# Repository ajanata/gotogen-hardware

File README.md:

# Gotogen Hardware

Protogen, the Go way. This repository is the entrypoint for hardware devices.

Highly volatile during active development. For ease of my own development, there are `replace` directives in `go.mod` to use relative paths for the related modules (`go.work` wasn't working for me). I will attempt to keep all the repositories up to date. You will need to either remove the `replace` directives, or have all the repositories checked out next to each other.

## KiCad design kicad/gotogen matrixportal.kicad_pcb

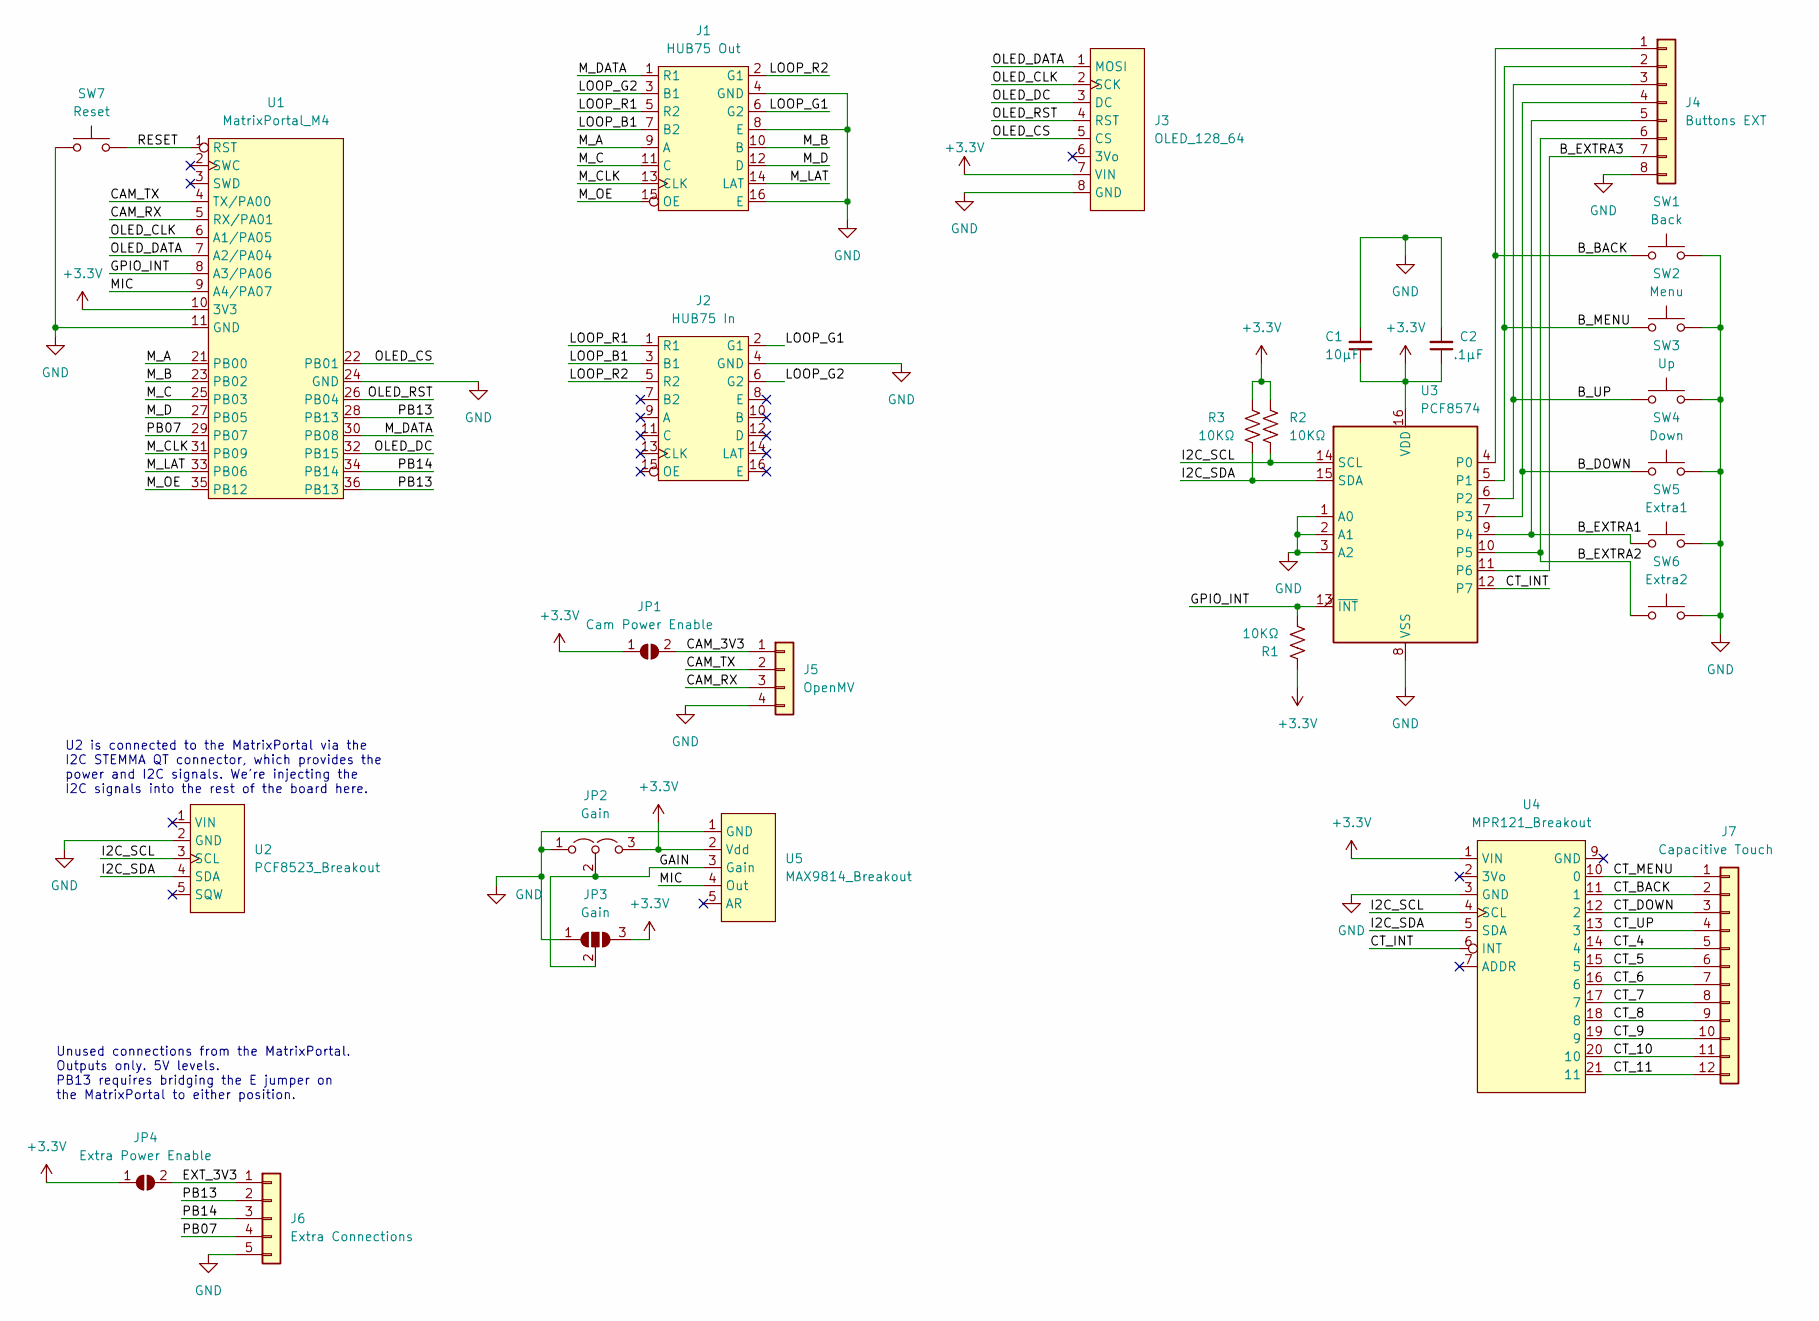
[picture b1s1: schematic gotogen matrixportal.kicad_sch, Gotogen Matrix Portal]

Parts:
C1: 10μF; C_Disc_D5.0mm_W2.5mm_P5.00mm
C2: .1μF; C_Disc_D5.0mm_W2.5mm_P5.00mm
J1: HUB75 Out; PinSocket_2x08_P2.54mm_Vertical
J2: HUB75 In; PinHeader_2x08_P2.54mm_Vertical
J3: OLED_128_64
J4: Buttons EXT; PinHeader_1x08_P2.54mm_Vertical
J5: OpenMV; PinHeader_1x04_P2.54mm_Vertical
J6: Extra Connections; PinHeader_1x05_P2.54mm_Vertical
J7: Capacitive Touch; PinHeader_1x12_P2.54mm_Vertical
JP1: Cam Power Enable; SolderJumper-2_P1.3mm_Open_Pad1.0x1.5mm
JP2: Gain; PinHeader_1x03_P2.54mm_Vertical
JP3: Gain; SolderJumper-3_P1.3mm_Open_Pad1.0x1.5mm_NumberLabels
JP4: Extra Power Enable; SolderJumper-2_P1.3mm_Open_Pad1.0x1.5mm
R1, R2, R3: 10KΩ; R_Axial_DIN0207_L6.3mm_D2.5mm_P7.62mm_Horizontal
SW1: Back; SW_PUSH_6mm
SW2: Menu; SW_PUSH_6mm
SW3: Up; SW_PUSH_6mm
SW4: Down; SW_PUSH_6mm
SW5: Extra1; SW_PUSH_6mm
SW6: Extra2; SW_PUSH_6mm
SW7: Reset; SW_PUSH_6mm
U1: MatrixPortal_M4; MatrixPortal M4
U2: PCF8523_Breakout; PCF8523 Breakout
U3: PCF8574; DIP-16_W7.62mm
U4: MPR121_Breakout; MPR121 Breakout
U5: MAX9814_Breakout; MAX9814 Breakout

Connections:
+3.3V: C1.1, C2.1, J3.7 (VIN), JP1.1 (A), JP2.3 (B), JP3.3 (B), JP4.1 (A), R1.2, R2.2, R3.2, U1.10 (3V3), U3.16 (VDD), U4.1 (VIN), U5.2 (Vdd)
/B_BACK: J4.1, SW1.1, U3.4 (P0)
/B_DOWN: J4.4, SW4.1, U3.7 (P3)
/B_EXTRA1: J4.5, SW5.1, U3.9 (P4)
/B_EXTRA2: J4.6, SW6.1, U3.10 (P5)
/B_EXTRA3: J4.7, U3.11 (P6)
/B_MENU: J4.2, SW2.1, U3.5 (P1)
/B_UP: J4.3, SW3.1, U3.6 (P2)
/CAM_3V3: J5.1, JP1.2 (B)
/CAM_RX: J5.3, U1.5 (RX/PA01)
/CAM_TX: J5.2, U1.4 (TX/PA00)
/CT_4: J7.5, U4.14 (4)
/CT_5: J7.6, U4.15 (5)
/CT_6: J7.7, U4.16 (6)
/CT_7: J7.8, U4.17 (7)
/CT_8: J7.9, U4.18 (8)
/CT_9: J7.10, U4.19 (9)
/CT_10: J7.11, U4.20 (10)
/CT_11: J7.12, U4.21 (11)
/CT_BACK: J7.2, U4.11 (1)
/CT_DOWN: J7.3, U4.12 (2)
/CT_INT: U3.12 (P7), U4.6 (INT)
/CT_MENU: J7.1, U4.10 (0)
/CT_UP: J7.4, U4.13 (3)
/EXT_3V3: J6.1, JP4.2 (B)
/GAIN: JP2.2 (C), JP3.2 (C), U5.3 (Gain)
/GPIO_INT: R1.1, U1.8 (A3/PA06), U3.13 (~INT)
/I2C_SCL: R2.1, U2.3 (SCL), U3.14 (SCL), U4.4 (SCL)
/I2C_SDA: R3.1, U2.4 (SDA), U3.15 (SDA), U4.5 (SDA)
/LOOP_B1: J1.7 (B2), J2.3 (B1)
/LOOP_G1: J1.6 (G2), J2.2 (G1)
/LOOP_G2: J1.3 (B1), J2.6 (G2)
/LOOP_R1: J1.5 (R2), J2.1 (R1)
/LOOP_R2: J1.2 (G1), J2.5 (R2)
/MIC: U1.9 (A4/PA07), U5.4 (Out)
/M_A: J1.9 (A), U1.21 (PB00)
/M_B: J1.10 (B), U1.23 (PB02)
/M_C: J1.11 (C), U1.25 (PB03)
/M_CLK: J1.13 (CLK), U1.31 (PB09)
/M_D: J1.12 (D), U1.27 (PB05)
/M_DATA: J1.1 (R1), U1.30 (PB08)
/M_LAT: J1.14 (LAT), U1.33 (PB06)
/M_OE: J1.15 (OE), U1.35 (PB12)
/OLED_CLK: J3.2 (SCK), U1.6 (A1/PA05)
/OLED_CS: J3.5 (CS), U1.22 (PB01)
/OLED_DATA: J3.1 (MOSI), U1.7 (A2/PA04)
/OLED_DC: J3.3 (DC), U1.32 (PB15)
/OLED_RST: J3.4 (RST), U1.26 (PB04)
/PB07: J6.4, U1.29 (PB07)
/PB13: J6.2, U1.28 (PB13), U1.36 (PB13)
/PB14: J6.3, U1.34 (PB14)
/RESET: SW7.2, U1.1 (RST)
GND: C1.2, C2.2, J1.4 (GND), J1.8 (E), J1.16 (E), J2.4 (GND), J3.8 (GND), J4.8, J5.4, J6.5, JP2.1 (A), JP3.1 (A), SW1.2, SW2.2, SW3.2, SW4.2, SW5.2, SW6.2, SW7.1, U1.11 (GND), U1.24 (GND), U2.2 (GND), U3.1 (A0), U3.2 (A1), U3.3 (A2), U3.8 (VSS), U4.3 (GND), U5.1 (GND)

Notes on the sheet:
U2 is connected to the MatrixPortal via the I2C STEMMA QT connector, which provides the power and I2C signals. We're injecting the I2C signals into the rest of the board here.
Unused connections from the MatrixPortal. Outputs only. 5V levels. PB13 requires bridging the E jumper on the MatrixPortal to either position.

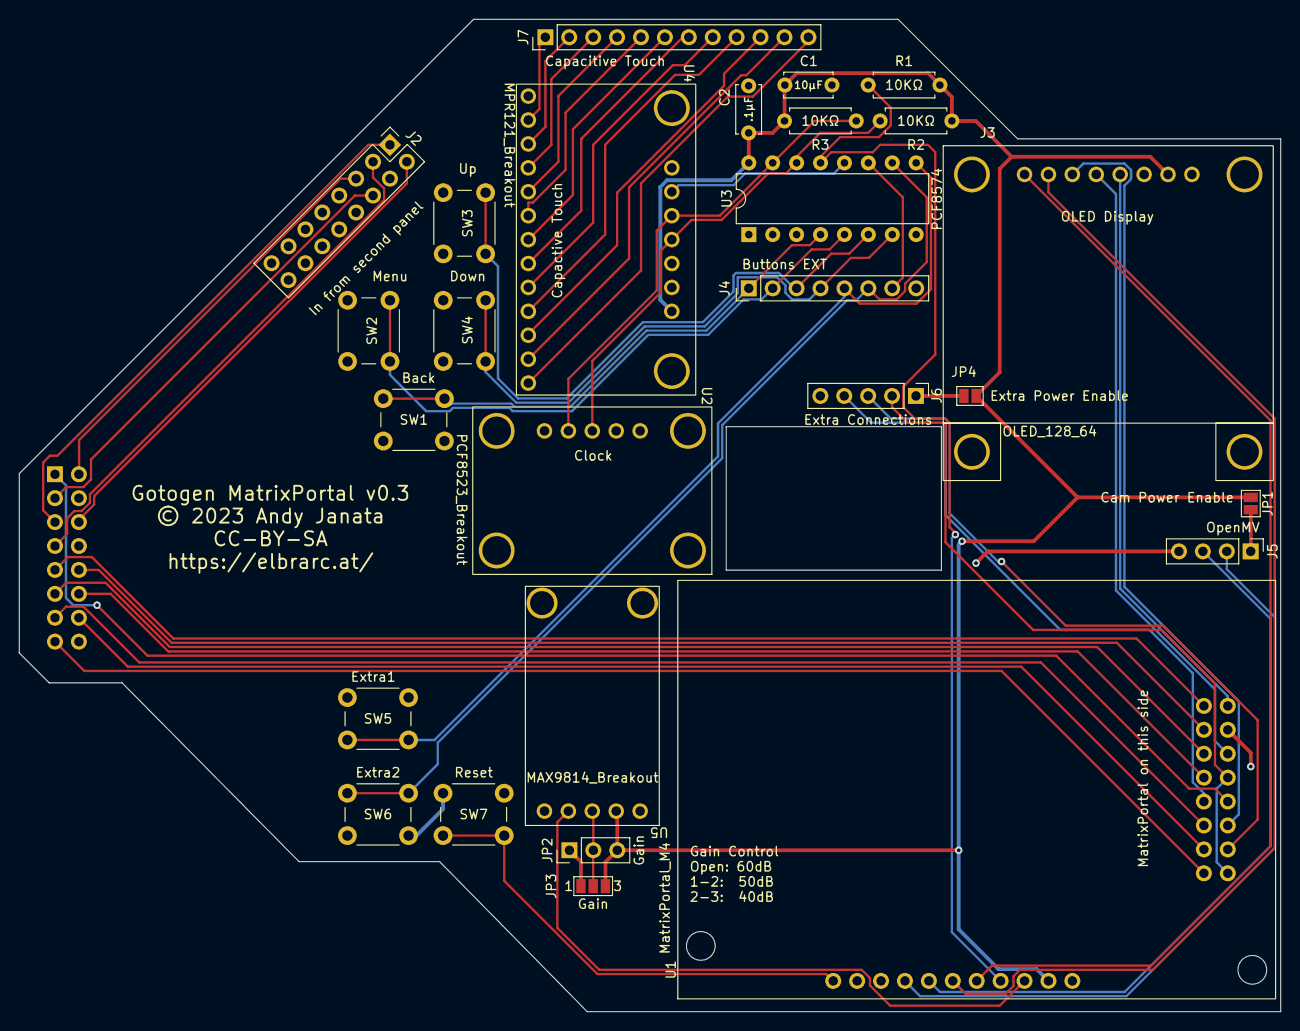
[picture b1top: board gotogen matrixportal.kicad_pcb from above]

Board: 2 copper layers, 134.0 x 105.4 mm, 28 parts (1 on the bottom side), 53 nets.

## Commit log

2022-10-16 initial commit
    split the microcontroller entrypoint out of the gotogen project so that project itself does not technically need the tinygo libraries. that effort may not be complete yet, but I want to get to that p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
2022-10-20 matrixportal-m4 support
2022-10-23 move pins around
2022-11-01 turn off the neopixel on boot
2022-11-02 cleanup, ntp, refactor
    * define the SPI bus we use here, so we don't depend on a hacky machine file in the tinygo runtime (except the hub75 driver still needs it for now)
    * use the esp32 coprocessor to get the current time from NTP on boot by connecting to a wifi network
    * refactor for gotogen changes, splitting init into early and late
2022-11-08 ntp refactor; button input
    * move ntp to its own package for reuse for other microcontrollers
    * implement the up and down buttons since they are on the matrixportal board and require no additional hardware work
2022-11-10 static allocation
2022-11-20 use refactored DMA drivers
2022-11-20 gotogen removed log parameter
2022-11-23 back and menu buttons
2022-11-25 more experimentation
2022-11-25 RTC, buttons, menu, prox, accelerometer
    * use an RTC chip if available and only NTP if it isn't there at all. I probably should make it sanity check the year because this seems to like to lose itself without realizing and say we're in the 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
    * implement all 4 main buttons
    * hardware menu to adjust face brightness and set the RTC via NTP
    * add proximity sensor for boop detection
    * add accelerometer for idle detection (eventually)
    * make ntp code able to be run more than once per boot
2022-11-26 time cleanup, qspi flash
    * don't wreck i2c while setting the rtc (oops)
    * set the runtime's timezone instead of trying to do the math ourselves
    * use littlefs on the matrixportal's flash chip. doesn't actually store anything useful here, but it gets initialized, and for some reason, simply starting to talk to it makes the whole thing at leas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
2022-11-28 add support for new Display interface
2022-11-28 stash mic
2022-12-05 trying to get oled on its own i2c
2022-12-07 more mic stuff, experiment probably works;
2022-12-11 update for PCB and accelerometer change
    * PCB will have LAT on a different pin, so using that now
    * accelerometer scale should be milligravity, not microgravity, for consistency with simulator
2022-12-12 getting really tired of this oled display
2023-01-18 rework mic driver
    instead of trying to be smart about it, just keep track of the standard deviation of the last however many samples. seems to work well enough for now
2023-01-18 experiment for mic
2023-01-18 mic, buttons, capacitive touch, oled spi
    * very low effort mic support. good enough to enable a talking animation
    * read buttons via PCF8574 GPIO expander
    * read MPR121 capacitive touch sensor for button input as well
    * move OLED to its own SPI bus (without DMA yet) for stability
2023-01-18 pcb
    kicad files for the pcb I made for this project
2023-01-20 first pass at pcb update
2023-01-21 further pcb updates
2023-01-21 completely rework PCB layout
    needed to get the matrixportal further away from my face, which required
    moving just about everything around
2023-01-22 move mounting holes
2023-01-23 add some missing silkscreen
2023-02-22 boot tweaks
    * enable cache controller immediately to improve execution speed during boot. previously, was enabled as a side effect of the QSPI driver for the flash chip
    * turn the neopixel on to a purple color during boot, then turn it off at the end of boot. it previously wasn't actually turning off on the first boot after a power cycle; not sure why doing it this 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
2023-04-26 DMA SPI for OLED; capacitive touch toggle
    Whoops, I never committed the DMA SPI stuff for the OLED, so that's getting combined with this other work because I'm too lazy to `git add -p`.
    * OLED status display is using DMA SPI now. This works very well for me.
    * Add a toggle for processing capacitive touch input by using one of the extra button inputs.
    * Fix some of the button ordering to match the silkscreen on the PCB.
2024-01-11 hack: extra capacitive touch inputs count as menu
2024-01-13 add mic toggle button
2024-11-06 fixes for drivers update
2024-11-06 need port for ntp

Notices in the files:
kicad/gotogen matrixportal.kicad_pcb:
© 2023 Andy Janata
CC-BY-SA
